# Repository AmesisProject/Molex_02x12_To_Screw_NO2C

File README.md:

# Speeduino Molex_02x12_To_Screw_NO2C

 Conector Plug for NO2C Speedy Board Speeduino
Molex to Screw Terminal

For SpeedyBoard https://github.com/turboedge/SpeedyBoards

View BOM Here 
https://htmlpreview.github.io/?https://github.com/AmesisProject/Molex_02x12_To_Screw_NO2C/blob/main/Kicad/v0.1/bom/ibom.html

TerminalBlock_Phoenix_PT-1,5-12-3.5-H_1x12_P3.50mm_Horizontal

AmesisProject YouTube https://www.youtube.com/channel/UCCexVZN3UYSep2lsj2jVjdg

WebSite https://sites.google.com/view/amesis-project/accueil?authuser=1

Donate https://www.paypal.com/donate/?cmd=_s-xclick&hosted_button_id=R9SMSS8L6FZB2&source=url

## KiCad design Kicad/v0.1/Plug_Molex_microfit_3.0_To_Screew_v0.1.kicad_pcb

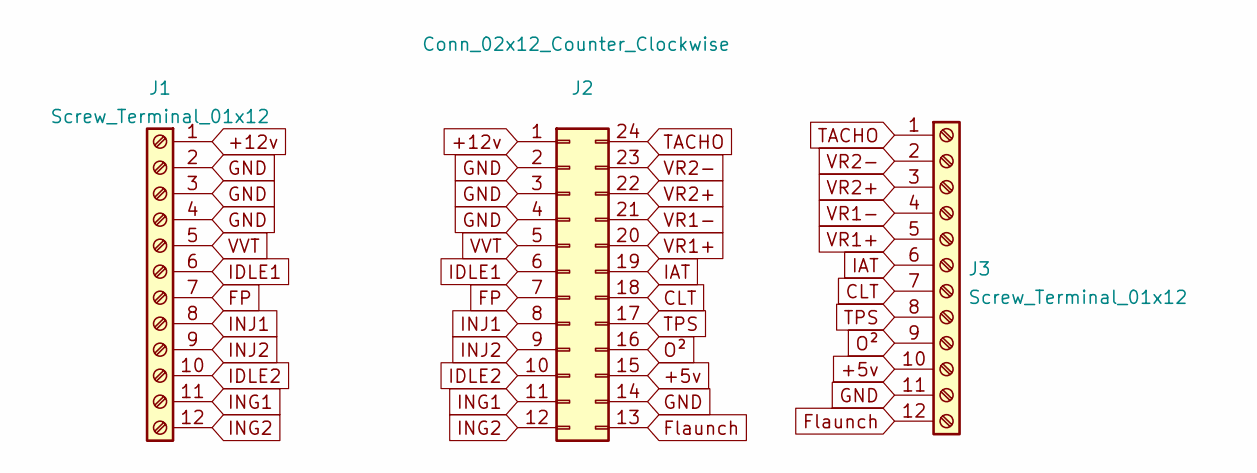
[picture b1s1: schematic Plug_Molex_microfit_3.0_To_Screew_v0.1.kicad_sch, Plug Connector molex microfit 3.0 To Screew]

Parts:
J1, J3: Screw_Terminal_01x12; TerminalBlock_4Ucon_1x12_P3.50mm_Horizontal
J2: Conn_02x12_Counter_Clockwise; Molex_Micro-Fit_3.0_43045-2400_2x12_P3.00mm_Horizontal

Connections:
+5v: J2.15, J3.10
+12v: J1.1, J2.1
CLT: J2.18, J3.7
FP: J1.7, J2.7
Flaunch: J2.13, J3.12
GND: J1.2, J1.3, J1.4, J2.2, J2.3, J2.4, J2.14, J3.11
IAT: J2.19, J3.6
IDLE1: J1.6, J2.6
IDLE2: J1.10, J2.10
ING1: J1.11, J2.11
ING2: J1.12, J2.12
INJ1: J1.8, J2.8
INJ2: J1.9, J2.9
O²: J2.16, J3.9
TACHO: J2.24, J3.1
TPS: J2.17, J3.8
VR1+: J2.20, J3.5
VR1-: J2.21, J3.4
VR2+: J2.22, J3.3
VR2-: J2.23, J3.2
VVT: J1.5, J2.5

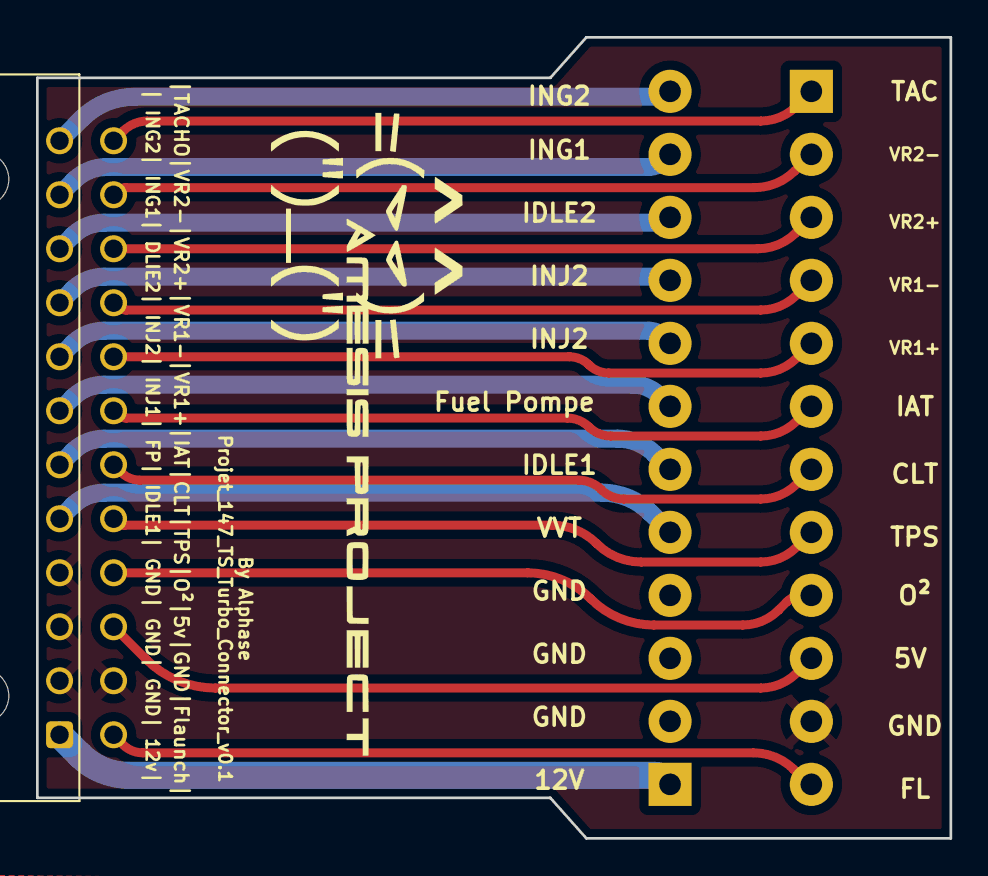
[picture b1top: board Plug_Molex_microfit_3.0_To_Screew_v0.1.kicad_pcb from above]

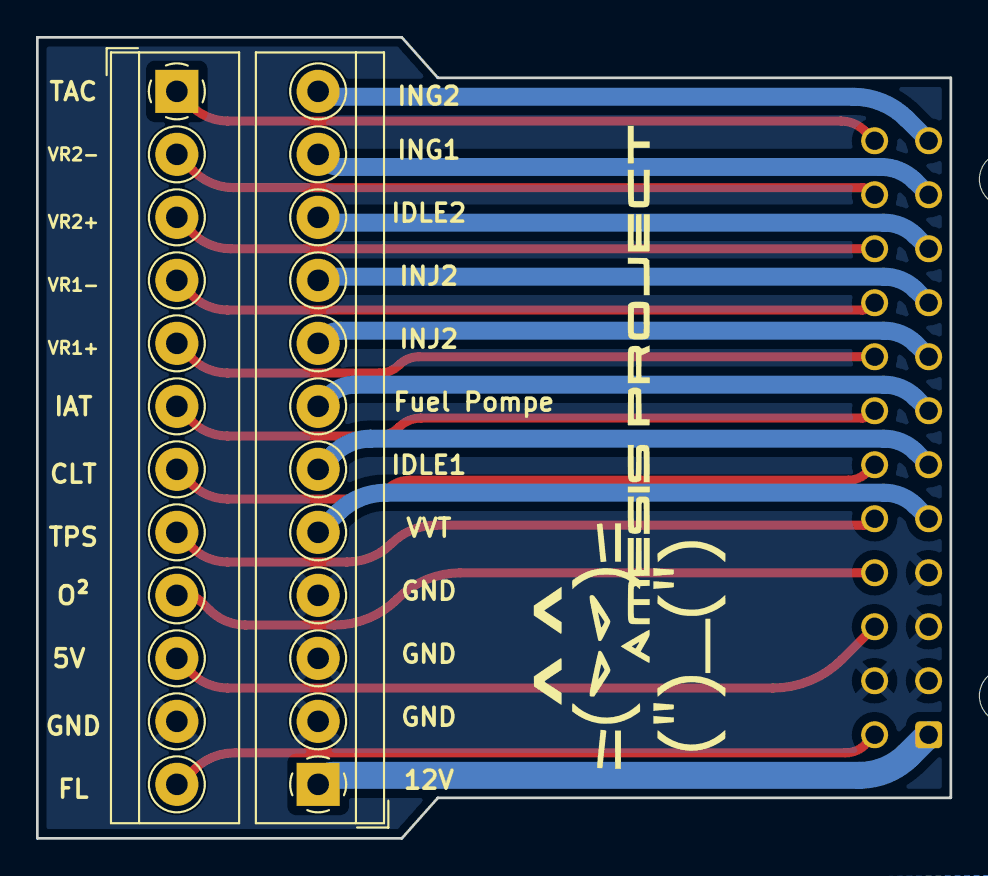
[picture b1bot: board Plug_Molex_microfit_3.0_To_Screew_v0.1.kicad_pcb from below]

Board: 2 copper layers, 50.8 x 44.5 mm, 3 parts (2 on the bottom side), 21 nets.

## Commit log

2022-04-25 Kicad
    Création du fichier Kicad
2022-04-26 Création des Gerbers et Drill
2022-04-26 Photos
